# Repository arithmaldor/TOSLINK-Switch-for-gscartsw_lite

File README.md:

# Copyright and Disclaimer
Copyright: Jacob Proctor 2018

This documentation describes Open Hardware and is licensed under the
CERN OHL v. 1.2.

You may redistribute and modify this documentation under the terms of the
CERN OHL v.1.2. (http://ohwr.org/cernohl). This documentation is distributed
WITHOUT ANY EXPRESS OR IMPLIED WARRANTY, INCLUDING OF
MERCHANTABILITY, SATISFACTORY QUALITY AND FITNESS FOR A
PARTICULAR PURPOSE. Please see the CERN OHL v.1.2 for applicable
conditions

# TOSLINK Switch for gscartsw_lite
8 port TOSLINK switch for gscartsw_lite that automatically follows the input. I was unable to get this working, will need to power the circuit externally? Or the problem could be something else.

# BOM
TOSLINK input: Sharp GP1FA551RZ Toslink Receiver	

TOSLINK output: Sharp GP1FA551TZ or PL131 Toslink Receiver	

U1: SN74CBT3251 1: 8 Mux	TSSOP16

C1-C9: 100 nF ceramic capacitor		0805

U2: 8 pin header, 2.54mm spacing

100uF 7343 Tantalum Capacitor x1

## OSH Park
Find this project on OSh Park: https://oshpark.com/shared_projects/WhT3B602

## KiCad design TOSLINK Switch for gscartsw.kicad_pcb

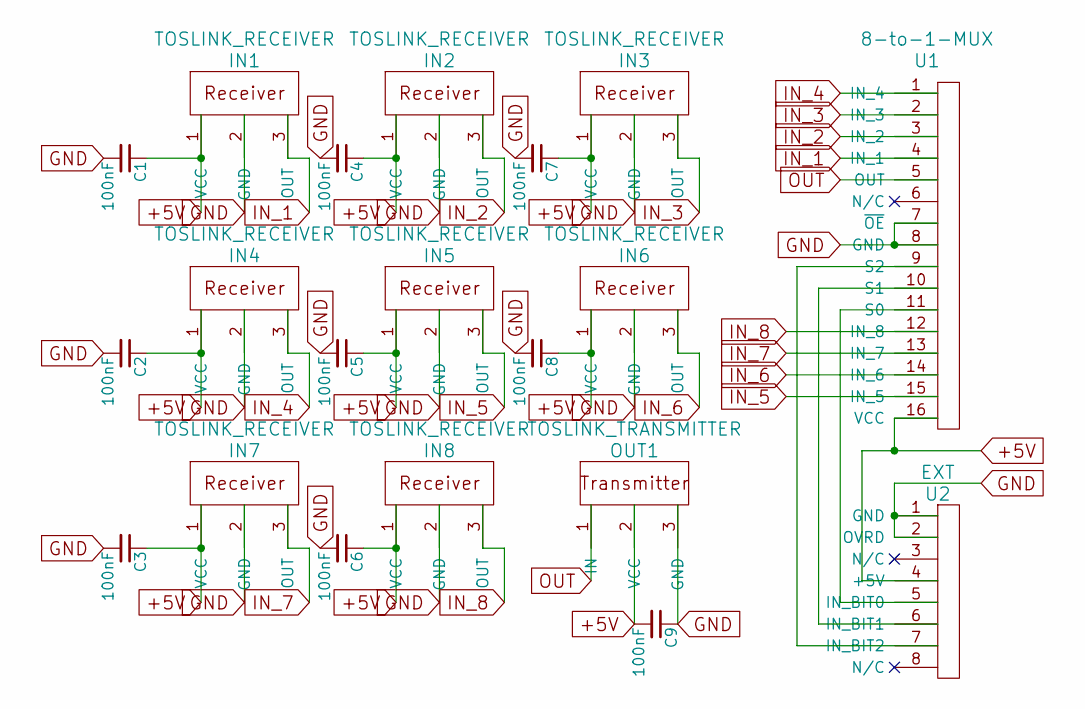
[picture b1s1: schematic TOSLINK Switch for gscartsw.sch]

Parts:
C1, C2, C3, C4, C5, C6, C7, C8, C9: 100nF; C_0805_HandSoldering
IN1, IN2, IN3, IN4, IN5, IN6, IN7, IN8: TOSLINK_RECEIVER; TOSLINK REC
OUT1: TOSLINK_TRANSMITTER; TOSLIN_TRNS
U1: 8-to-1-MUX; TSSOP-16_4.4x5mm_Pitch0.65mm
U2: EXT; Pin_Header_Straight_2x04_Pitch2.54mm

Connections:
+5V: C1.1, C2.1, C3.1, C4.1, C5.1, C6.1, C7.1, C8.1, C9.2, IN1.1 (VCC), IN2.1 (VCC), IN3.1 (VCC), IN4.1 (VCC), IN5.1 (VCC), IN6.1 (VCC), IN7.1 (VCC), IN8.1 (VCC), OUT1.2 (VCC), U1.16 (VCC), U2.4 (+5V); also elsewhere on the board
GND: C1.2, C2.2, C3.2, C4.2, C5.2, C6.2, C7.2, C8.2, C9.1, IN1.2 (GND), IN2.2 (GND), IN3.2 (GND), IN4.2 (GND), IN5.2 (GND), IN6.2 (GND), IN7.2 (GND), IN8.2 (GND), OUT1.3 (GND), U1.7 (~OE~), U1.8 (GND), U2.1 (GND), U2.2 (OVRD); also elsewhere on the board
IN_1: IN1.3 (OUT), U1.4 (IN_1)
IN_2: IN2.3 (OUT), U1.3 (IN_2)
IN_3: IN3.3 (OUT), U1.2 (IN_3)
IN_4: IN4.3 (OUT), U1.1 (IN_4)
IN_5: IN5.3 (OUT), U1.15 (IN_5)
IN_6: IN6.3 (OUT), U1.14 (IN_6)
IN_7: IN7.3 (OUT), U1.13 (IN_7)
IN_8: IN8.3 (OUT), U1.12 (IN_8)
unnamed: U1.9 (S2), U2.7 (IN_BIT2)
unnamed: U1.10 (S1), U2.6 (IN_BIT1)
unnamed: U1.11 (S0), U2.5 (IN_BIT0)
OUT: OUT1.1 (IN), U1.5 (OUT)

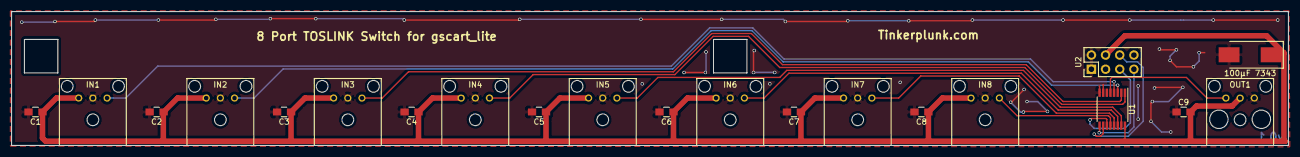
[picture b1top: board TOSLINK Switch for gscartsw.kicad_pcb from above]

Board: 2 copper layers, 228.9 x 24.0 mm, 21 parts (0 on the bottom side), 14 nets.

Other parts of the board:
100μF 7343: CP_Tantalum_Case-D_EIA-7343-31_Hand

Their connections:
+5V: 100μF 7343.1; also elsewhere on the board
GND: 100μF 7343.2; also elsewhere on the board

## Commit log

2018-06-30 Version 0.1
    Untested
2018-06-30 added tantalum cap
2018-07-29 Datasheets
    Added datasheets folder for references
2019-04-22 Update Readme
    Added note to say that it doesn't work.
2020-07-02 Create fp-info-cache
